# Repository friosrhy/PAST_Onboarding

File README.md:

# PAST_Onboarding
PAST Onboarding Repo

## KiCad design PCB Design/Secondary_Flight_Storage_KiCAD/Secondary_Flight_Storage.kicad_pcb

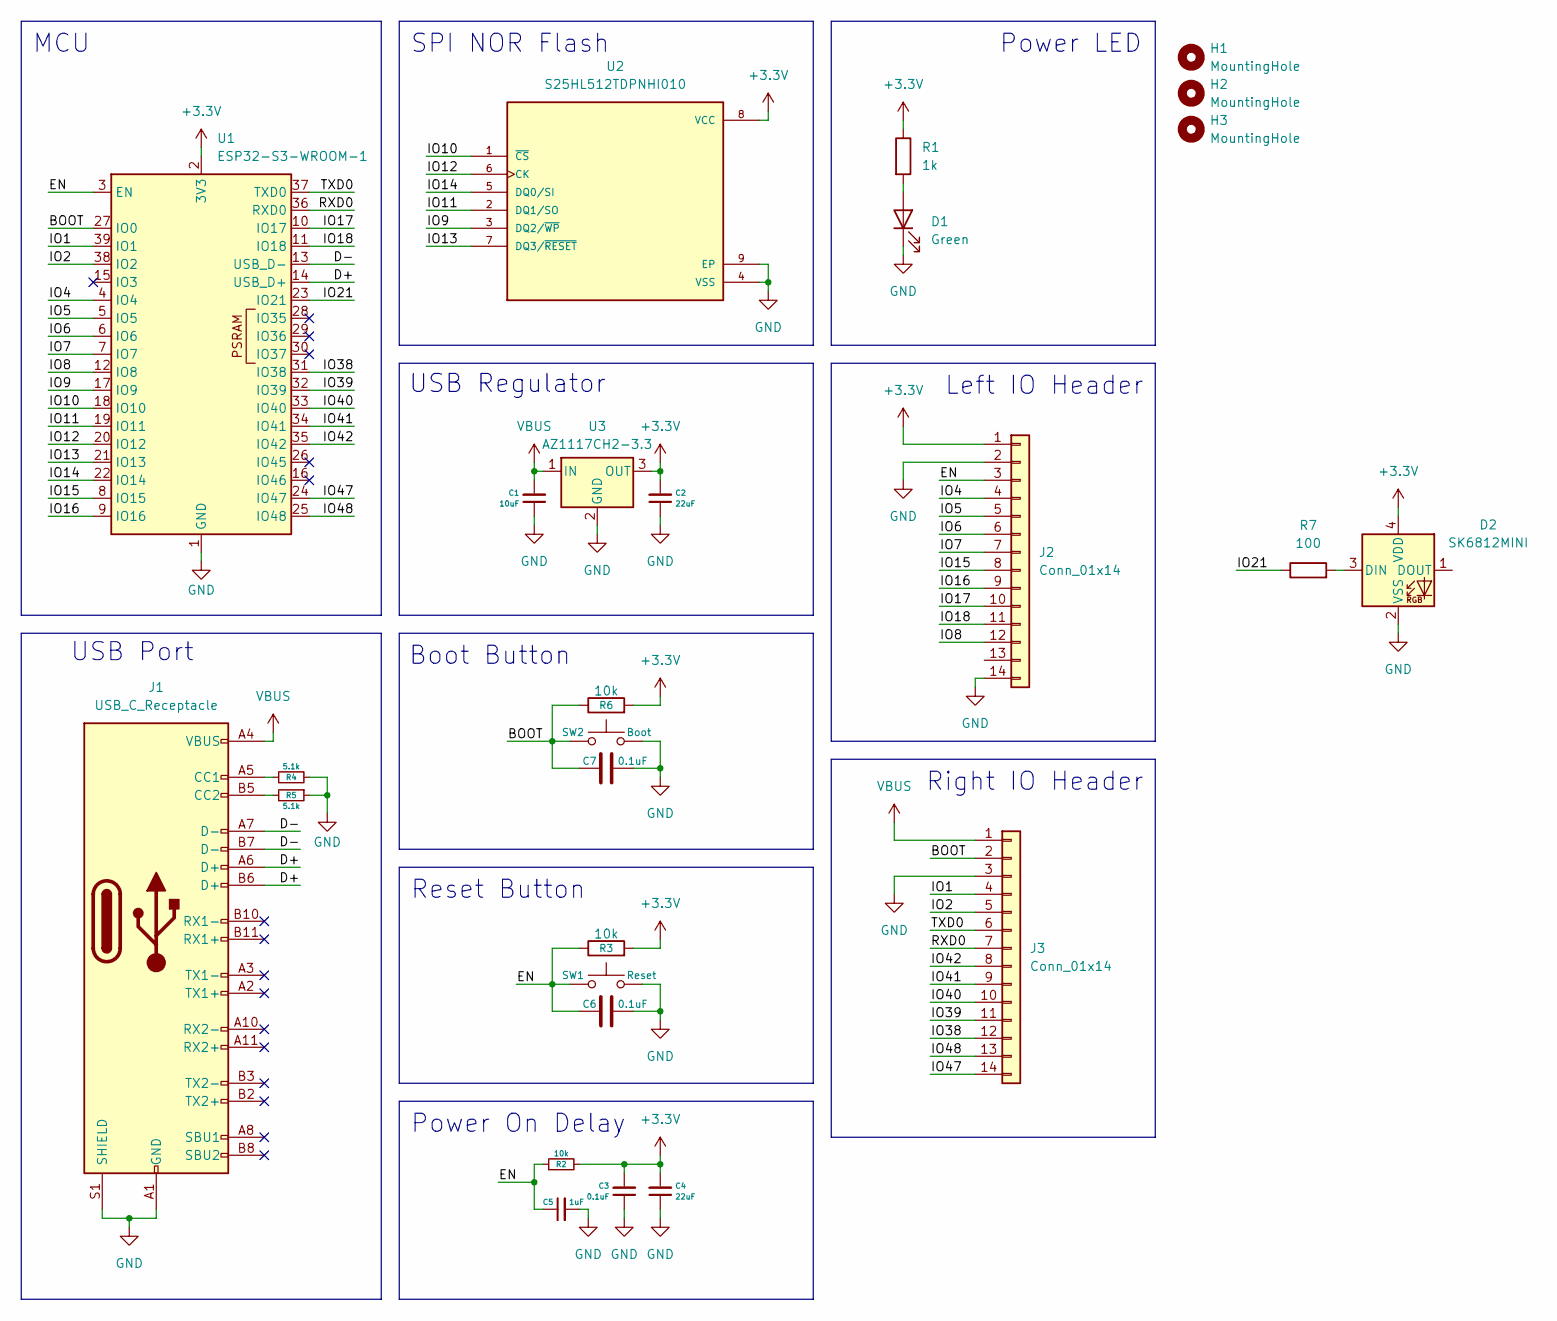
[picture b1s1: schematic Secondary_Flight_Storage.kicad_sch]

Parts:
C1: 10uF; C_0603_1608Metric_Pad1.08x0.95mm_HandSolder
C2, C4: 22uF; C_0603_1608Metric_Pad1.08x0.95mm_HandSolder
C3, C6, C7: 0.1uF; C_0603_1608Metric_Pad1.08x0.95mm_HandSolder
C5: 1uF; C_0603_1608Metric_Pad1.08x0.95mm_HandSolder
D1: Green; LED_0603_1608Metric_Pad1.05x0.95mm_HandSolder
D2: SK6812MINI; LED_SK6812MINI_PLCC4_3.5x3.5mm_P1.75mm
H1, H2, H3: MountingHole; MountingHole_2.2mm_M2
J1: USB_C_Receptacle; USB_C_Receptacle_GCT_USB4105-xx-A_16P_TopMnt_Horizontal
J2, J3: Conn_01x14; PinHeader_1x14_P2.54mm_Vertical
R1: 1k; R_0603_1608Metric_Pad0.98x0.95mm_HandSolder
R2, R3, R6: 10k; R_0603_1608Metric_Pad0.98x0.95mm_HandSolder
R4, R5: 5.1k; R_0603_1608Metric_Pad0.98x0.95mm_HandSolder
R7: 100; R_0603_1608Metric_Pad0.98x0.95mm_HandSolder
SW1: Reset; SW_SPST_B3U-1000P
SW2: Boot; SW_SPST_B3U-1000P
U1: ESP32-S3-WROOM-1; ESP32-S3-WROOM-1U
U2: S25HL512TDPNHI010; SON127P600X800X80-9N; PARTREV AB; DigiKey_Part_Number 448-S25HL512TDPNHI010-ND
U3: AZ1117CH2-3.3; SOT-223-3_TabPin2

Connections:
+3.3V: C2.2, C3.2, C4.2, D2.4 (VDD), J2.1, R1.1, R2.2, R3.2, R6.2, U1.2 (3V3), U2.8 (VCC), U3.3 (OUT)
/BOOT: C7.1, J3.2, R6.1, SW2.1, U1.27 (IO0)
/D+: J1.A6 (D+), J1.B6 (D+), U1.14 (USB_D+)
/D-: J1.A7 (D-), J1.B7 (D-), U1.13 (USB_D-)
/EN: C5.1, C6.1, J2.3, R2.1, R3.1, SW1.1, U1.3 (EN)
/IO1: J3.4, U1.39 (IO1)
/IO2: J3.5, U1.38 (IO2)
/IO4: J2.4, U1.4 (IO4)
/IO5: J2.5, U1.5 (IO5)
/IO6: J2.6, U1.6 (IO6)
/IO7: J2.7, U1.7 (IO7)
/IO8: J2.12, U1.12 (IO8)
/IO9: U1.17 (IO9), U2.3 (DQ2/~WP)
/IO10: U1.18 (IO10), U2.1 (~CS)
/IO11: U1.19 (IO11), U2.2 (DQ1/SO)
/IO12: U1.20 (IO12), U2.6 (CK)
/IO13: U1.21 (IO13), U2.7 (DQ3/~RESET)
/IO14: U1.22 (IO14), U2.5 (DQ0/SI)
/IO15: J2.8, U1.8 (IO15)
/IO16: J2.9, U1.9 (IO16)
/IO17: J2.10, U1.10 (IO17)
/IO18: J2.11, U1.11 (IO18)
/IO21: R7.1, U1.23 (IO21)
/IO38: J3.12, U1.31 (IO38)
/IO39: J3.11, U1.32 (IO39)
/IO40: J3.10, U1.33 (IO40)
/IO41: J3.9, U1.34 (IO41)
/IO42: J3.8, U1.35 (IO42)
/IO47: J3.14, U1.24 (IO47)
/IO48: J3.13, U1.25 (IO48)
/RXD0: J3.7, U1.36 (RXD0)
/TXD0: J3.6, U1.37 (TXD0)
GND: C1.1, C2.1, C3.1, C4.1, C5.2, C6.2, C7.2, D1.1 (K), D2.2 (VSS), J1.A1 (GND), J1.A12 (GND), J1.B1 (GND), J1.B12 (GND), J1.S1 (SHIELD), J2.2, J2.14, J3.3, R4.2, R5.1, SW1.2, SW2.2, U1.1 (GND), U1.40 (GND), U1.41 (GND), U2.4 (VSS), U2.9 (EP), U3.2 (GND)
unnamed: D1.2 (A), R1.2
unnamed: D2.3 (DIN), R7.2
unnamed: J1.A5 (CC1), R4.1
unnamed: J1.B5 (CC2), R5.2
VBUS: C1.2, J1.A4 (VBUS), J1.A9 (VBUS), J1.B4 (VBUS), J1.B9 (VBUS), J3.1, U3.1 (IN)

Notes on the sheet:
USB Regulator
Right IO Header
Boot Button
Reset Button
Left IO Header
Power On Delay
USB Port
MCU
SPI NOR Flash
Power LED

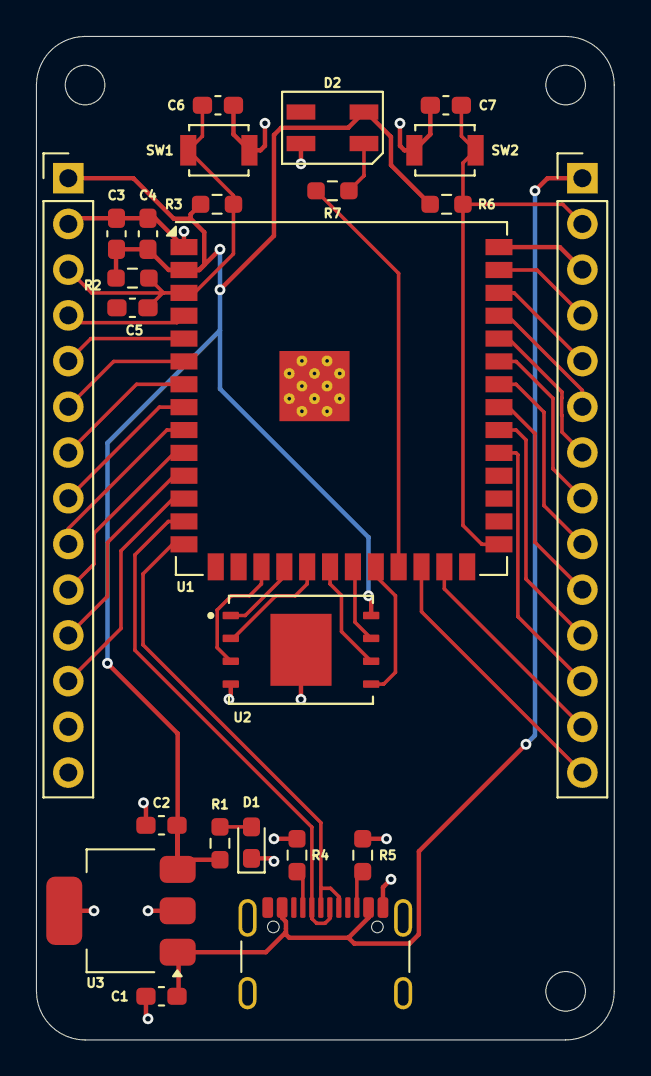
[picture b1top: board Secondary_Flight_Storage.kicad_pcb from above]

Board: 2 copper layers, 32.1 x 55.8 mm, 27 parts (0 on the bottom side), 38 nets.

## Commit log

2026-03-18 Added Logbook and Custom Point Font
2026-03-18 Added PDF Copy of logbook
2026-03-18 Fixed Stupid Errors
2026-03-25 Added project research document
2026-03-28 Added PCB project files and research document, updated logbook
2026-04-04 Updated logbook and began work on schematic
2026-04-04 Added updated logbook
2026-04-21 Added V2 PCB Design and updated logbook
2026-05-06 Updated logbook and PCB designs
2026-05-16 Final Commit: Finalised PCB design, updated logbook, and finished logbook design
